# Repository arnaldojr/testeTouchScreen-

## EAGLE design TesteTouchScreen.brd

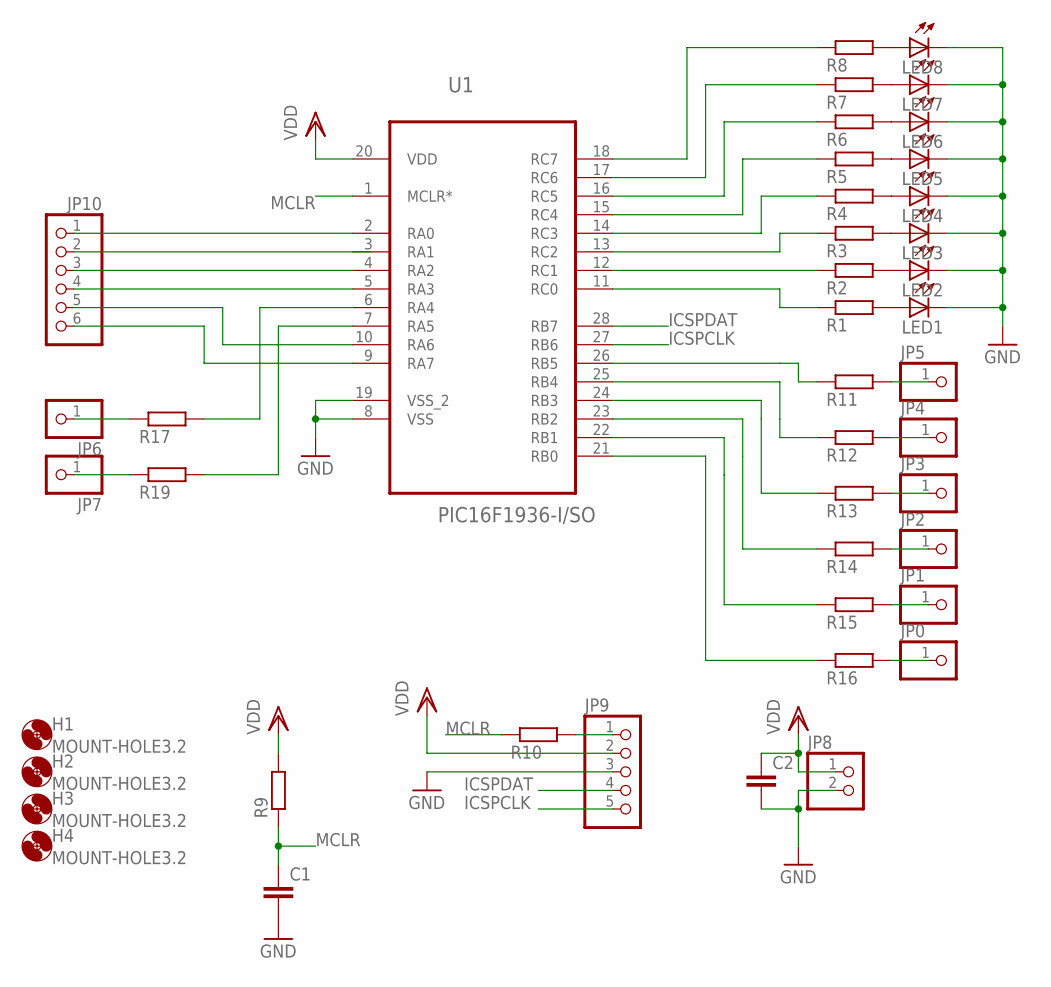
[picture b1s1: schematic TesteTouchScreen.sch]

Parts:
C1, C2: C-EUC1206; C1206
H1, H2, H3, H4: MOUNT-HOLE3.2; 3,2
JP0, JP1, JP2, JP3, JP4, JP5, JP6, JP7: PINHD-1X1; 1X01
JP8: PINHD-1X2; 1X02
JP9: PINHD-1X5; 1X05
JP10: PINHD-1X6; 1X06
LED1, LED2, LED3, LED4, LED5, LED6, LED7, LED8: LED5MM
R1, R2, R3, R4, R5, R6, R7, R8, R9, R10, R11, R12, R13, R14, R15, R16, R17, R19: R-EU_R0805; R0805
U1: PIC16F1936-I/SO; SOIC127P1030X265-28N

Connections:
GND: C1.2, C2.2, JP8.2, JP9.3, LED1.K (C), LED2.K (C), LED3.K (C), LED4.K (C), LED5.K (C), LED6.K (C), LED7.K (C), LED8.K (C), U1.8 (VSS), U1.19 (VSS_2)
ICSPCLK: JP9.5, U1.27 (RB6)
ICSPDAT: JP9.4, U1.28 (RB7)
MCLR: C1.1, R9.1, R10.1, U1.1 (MCLR*)
unnamed: JP6.1, R17.1
unnamed: JP7.1, R19.1
unnamed: JP0.1, R16.2
unnamed: JP1.1, R15.2
unnamed: JP2.1, R14.2
unnamed: JP3.1, R13.2
unnamed: JP5.1, R11.2
unnamed: R17.2, U1.6 (RA4)
unnamed: LED1.A, R1.2
unnamed: LED2.A, R2.2
unnamed: JP4.1, R12.2
unnamed: LED3.A, R3.2
unnamed: LED4.A, R4.2
unnamed: LED5.A, R5.2
unnamed: LED6.A, R6.2
unnamed: LED7.A, R7.2
unnamed: LED8.A, R8.2
unnamed: R1.1, U1.11 (RC0)
unnamed: R2.1, U1.12 (RC1)
unnamed: R3.1, U1.13 (RC2)
unnamed: R4.1, U1.14 (RC3)
unnamed: R5.1, U1.15 (RC4)
unnamed: R6.1, U1.16 (RC5)
unnamed: R7.1, U1.17 (RC6)
unnamed: R8.1, U1.18 (RC7)
unnamed: JP9.1, R10.2
unnamed: R19.2, U1.7 (RA5)
unnamed: R11.1, U1.26 (RB5)
unnamed: R12.1, U1.25 (RB4)
unnamed: R13.1, U1.24 (RB3)
unnamed: R14.1, U1.23 (RB2)
unnamed: R15.1, U1.22 (RB1)
unnamed: R16.1, U1.21 (RB0)
unnamed: JP10.1, U1.2 (RA0)
unnamed: JP10.3, U1.4 (RA2)
unnamed: JP10.4, U1.5 (RA3)
unnamed: JP10.5, U1.10 (RA6)
unnamed: JP10.6, U1.9 (RA7)
VDD: C2.1, JP8.1, JP9.2, R9.2, U1.20 (VDD)

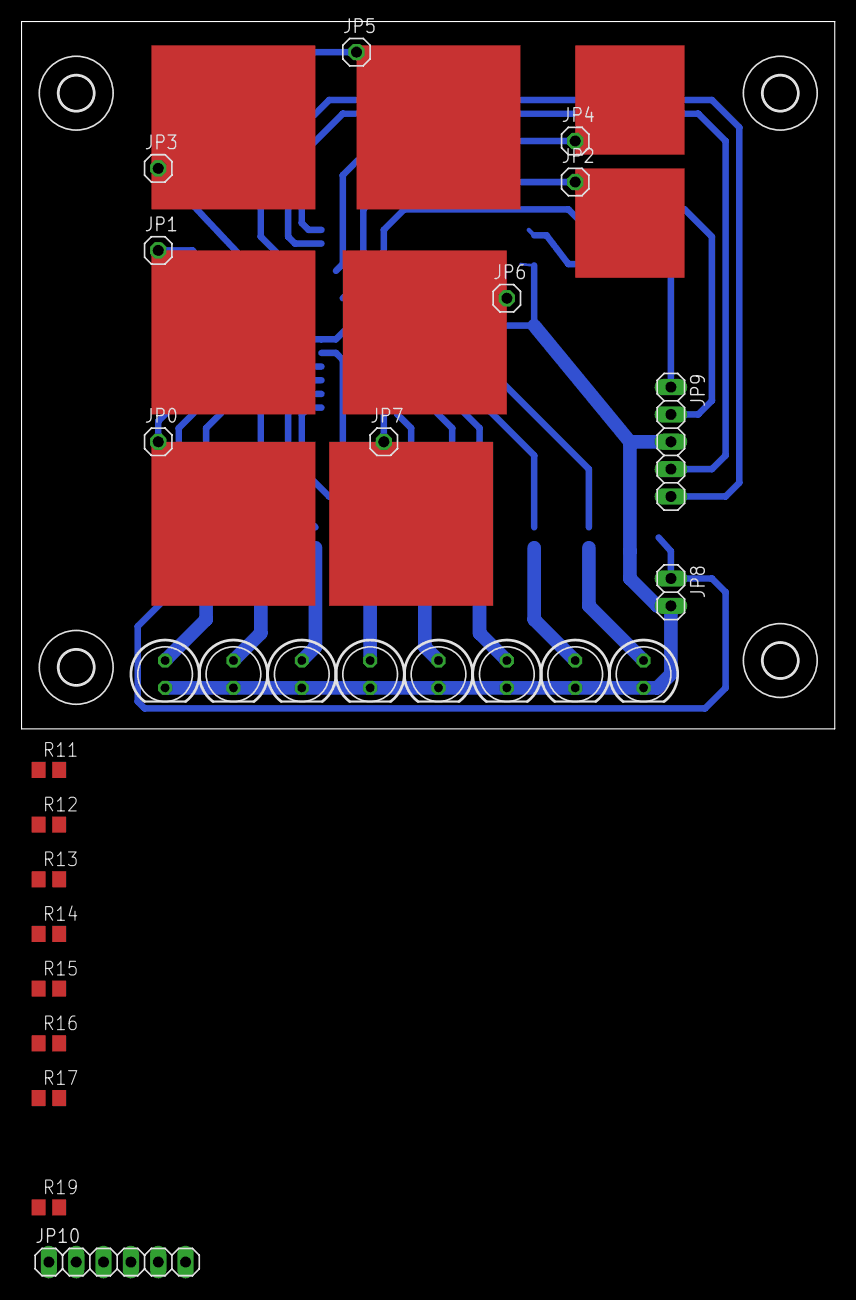
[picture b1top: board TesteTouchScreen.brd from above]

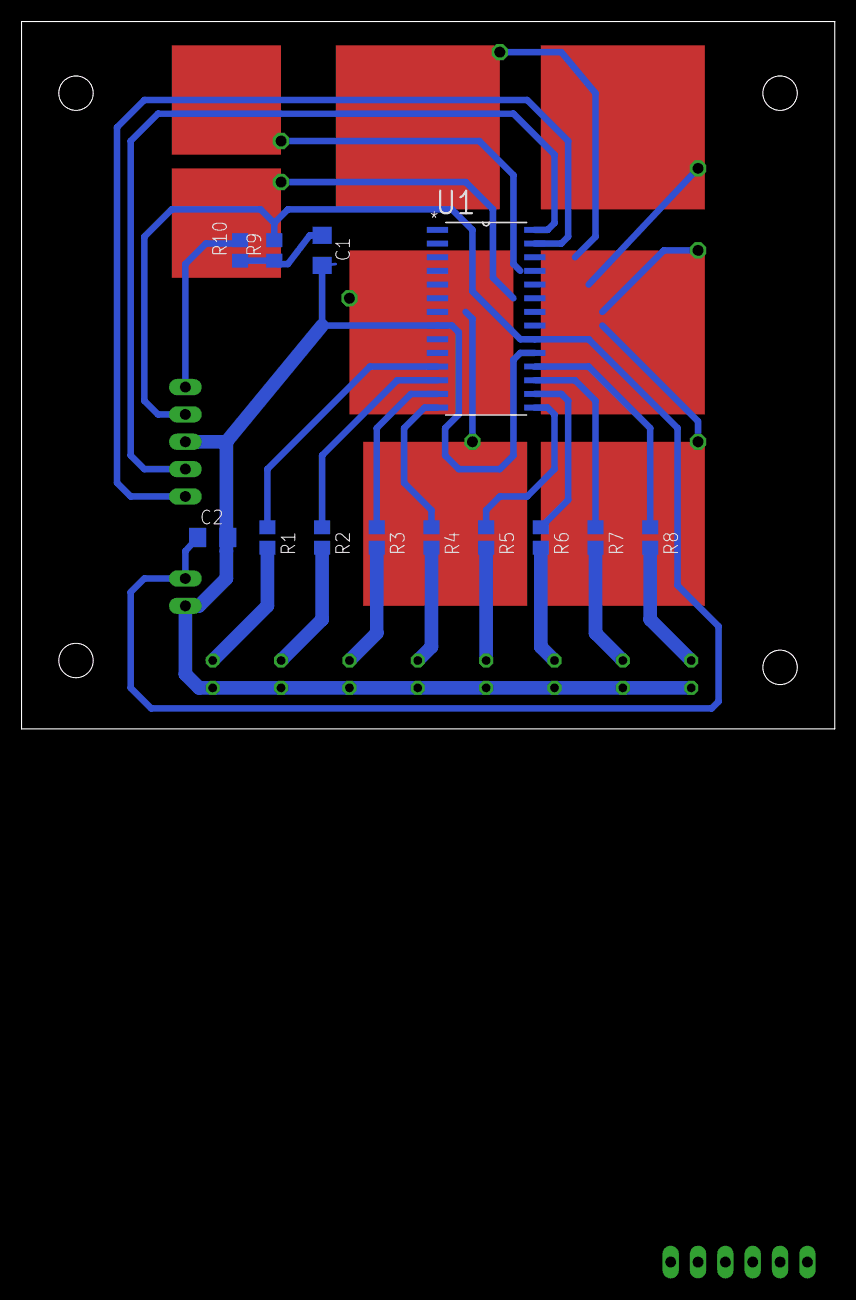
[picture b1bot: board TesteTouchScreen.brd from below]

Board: 2 copper layers, 75.5 x 65.7 mm, 44 parts (13 on the bottom side), 43 nets.

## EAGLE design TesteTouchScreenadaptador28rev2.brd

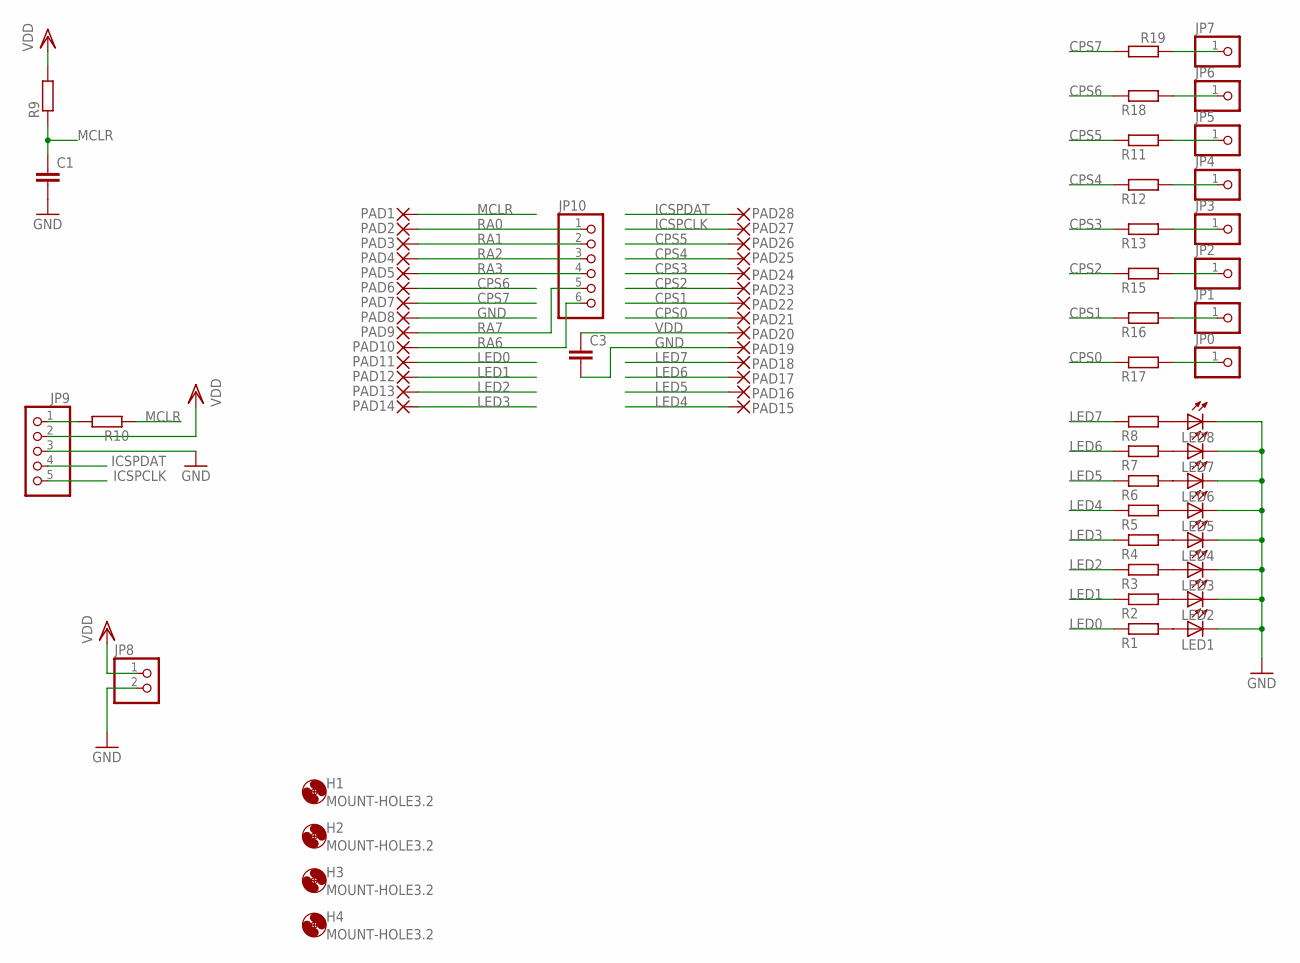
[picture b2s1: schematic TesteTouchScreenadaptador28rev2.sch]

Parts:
C1, C3: C-EUC1206; C1206
H1, H2, H3, H4: MOUNT-HOLE3.2; 3,2
JP0, JP1, JP2, JP3, JP4, JP5, JP6, JP7: PINHD-1X1; 1X01
JP8: PINHD-1X2; 1X02
JP9: PINHD-1X5; 1X05
JP10: PINHD-1X6; 1X06
LED1, LED2, LED3, LED4, LED5, LED6, LED7, LED8: LED5MM
PAD1, PAD2, PAD3, PAD4, PAD5, PAD6, PAD7, PAD8, PAD9, PAD10, PAD11, PAD12, PAD13, PAD14, PAD15, PAD16, PAD17, PAD18, PAD19, PAD20, PAD21, PAD22, PAD23, PAD24, PAD25, PAD26, PAD27, PAD28: SMD2; SMD1,27-2,54
R1, R2, R3, R4, R5, R6, R7, R8, R9, R10, R11, R12, R13, R15, R16, R17, R18, R19: R-EU_R0805; R0805

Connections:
CPS0: PAD21.1, R17.1
CPS1: PAD22.1, R16.1
CPS2: PAD23.1, R15.1
CPS3: PAD24.1, R13.1
CPS4: PAD25.1, R12.1
CPS5: PAD26.1, R11.1
CPS6: PAD6.1, R18.1
CPS7: PAD7.1, R19.2
GND: C1.2, C3.2, JP8.2, JP9.3, LED1.K (C), LED2.K (C), LED3.K (C), LED4.K (C), LED5.K (C), LED6.K (C), LED7.K (C), LED8.K (C), PAD8.1, PAD19.1
ICSPCLK: JP9.5, PAD27.1
ICSPDAT: JP9.4, PAD28.1
LED0: PAD11.1, R1.1
LED1: PAD12.1, R2.1
LED2: PAD13.1, R3.1
LED3: PAD14.1, R4.1
LED4: PAD15.1, R5.1
LED5: PAD16.1, R6.1
LED6: PAD17.1, R7.1
LED7: PAD18.1, R8.1
MCLR: C1.1, PAD1.1, R9.1, R10.1
unnamed: JP6.1, R18.2
unnamed: JP7.1, R19.1
unnamed: JP0.1, R17.2
unnamed: JP1.1, R16.2
unnamed: JP2.1, R15.2
unnamed: JP3.1, R13.2
unnamed: JP5.1, R11.2
unnamed: LED1.A, R1.2
unnamed: LED2.A, R2.2
unnamed: JP4.1, R12.2
unnamed: LED3.A, R3.2
unnamed: LED4.A, R4.2
unnamed: LED5.A, R5.2
unnamed: LED6.A, R6.2
unnamed: LED7.A, R7.2
unnamed: LED8.A, R8.2
unnamed: JP9.1, R10.2
RA0: JP10.1, PAD2.1
RA1: JP10.2, PAD3.1
RA2: JP10.3, PAD4.1
RA3: JP10.4, PAD5.1
RA6: JP10.6, PAD10.1
RA7: JP10.5, PAD9.1
VDD: C3.1, JP8.1, JP9.2, PAD20.1, R9.2

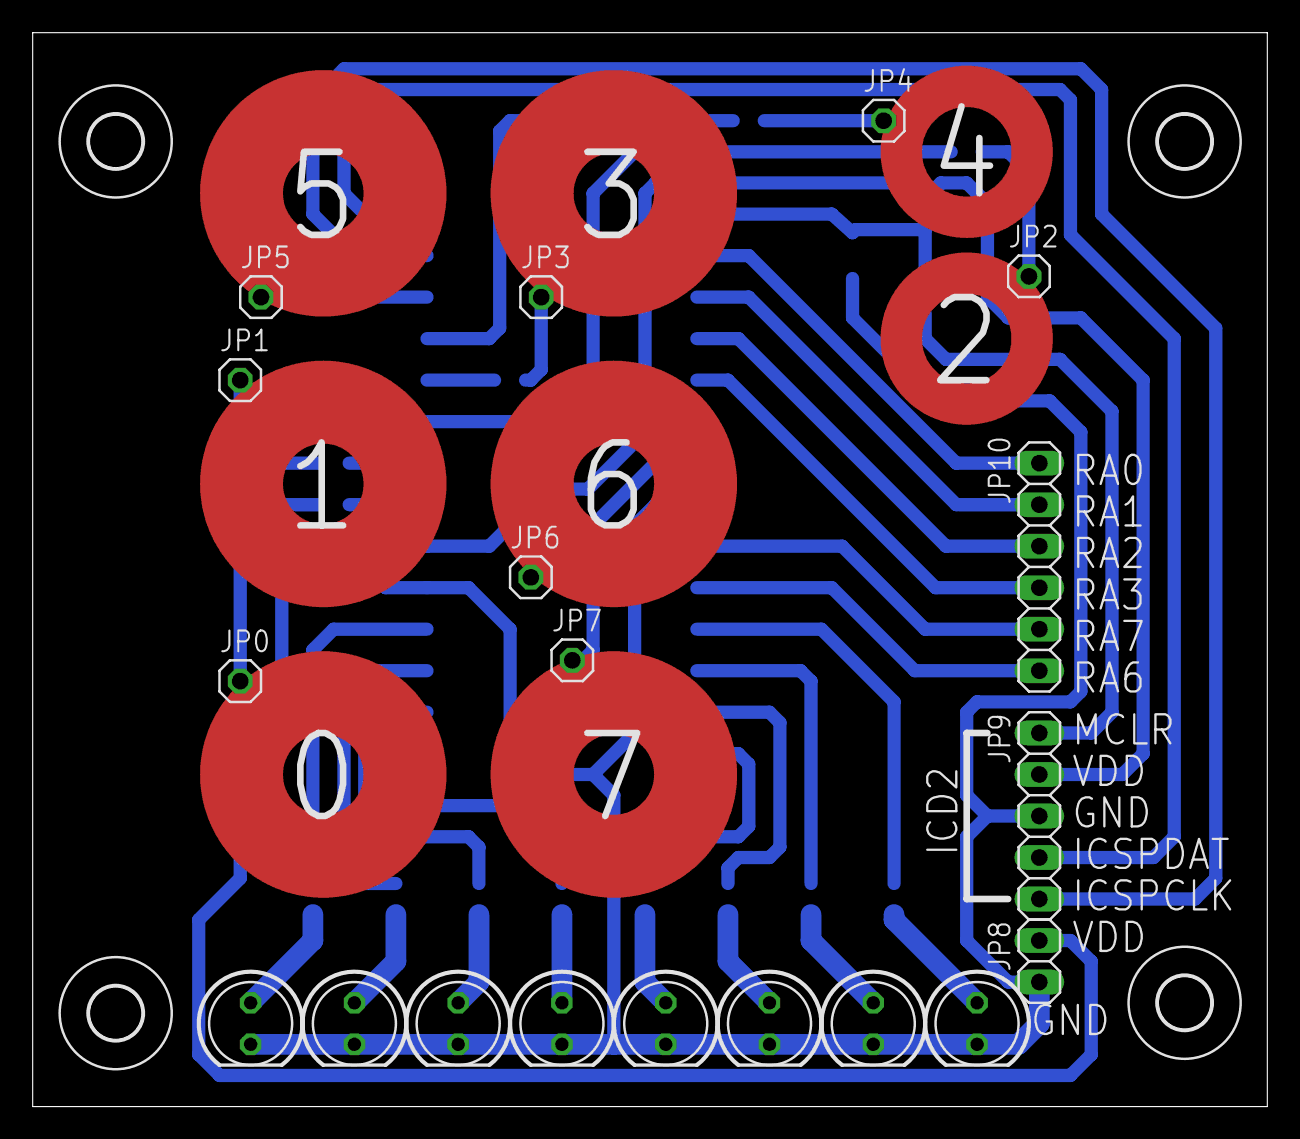
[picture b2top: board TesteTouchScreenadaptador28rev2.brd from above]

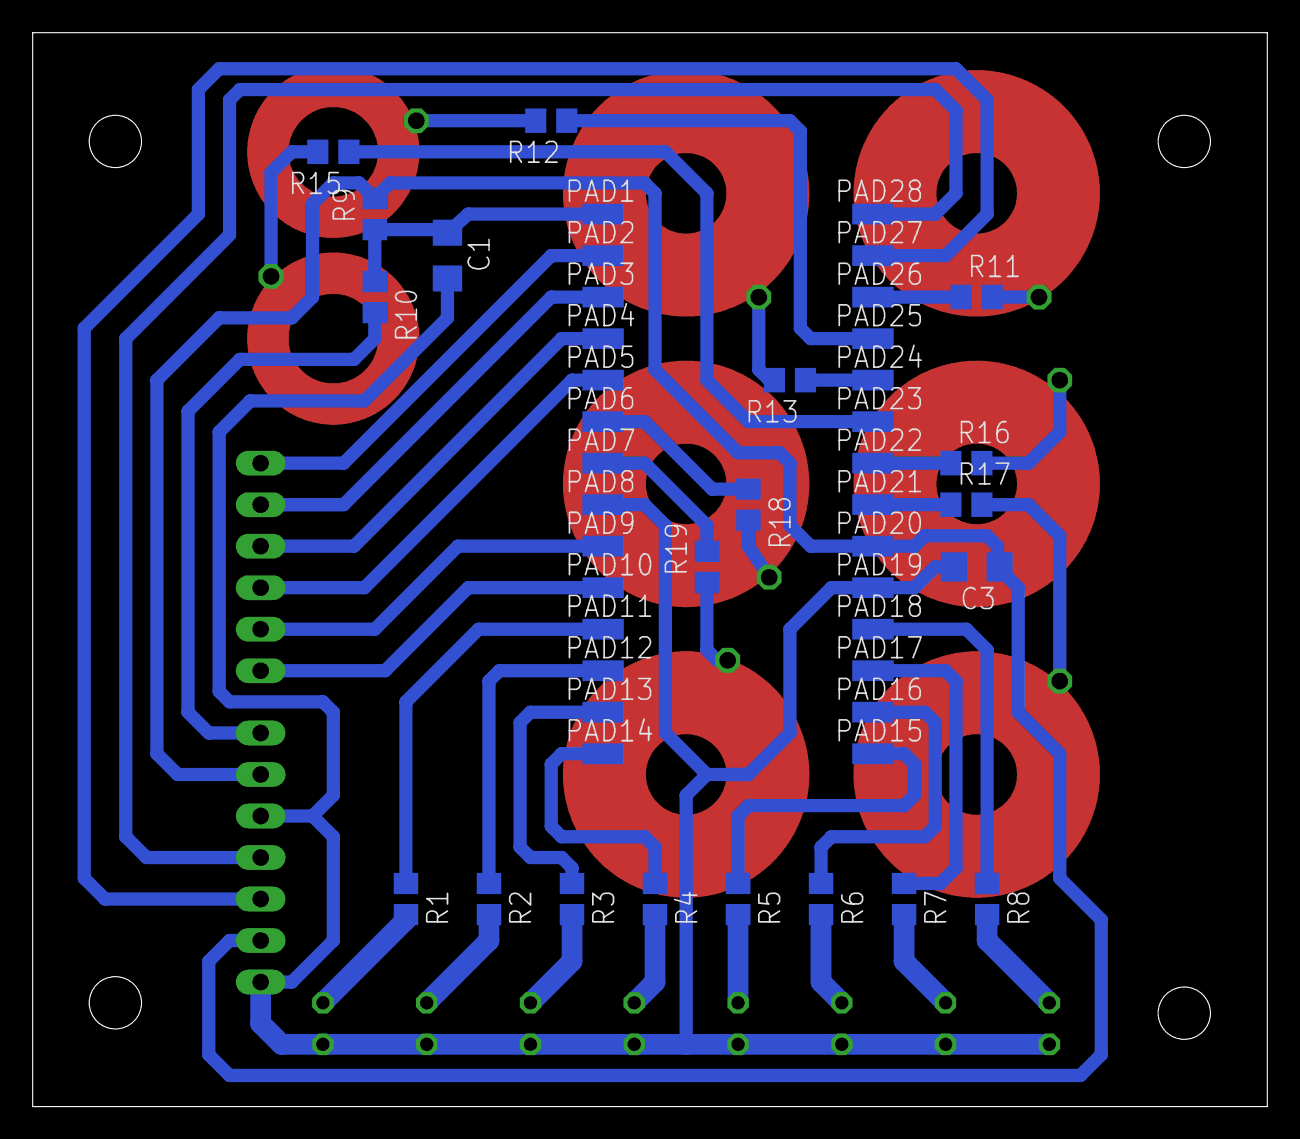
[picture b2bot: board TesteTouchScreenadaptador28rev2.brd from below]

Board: 2 copper layers, 75.5 x 65.7 mm, 71 parts (48 on the bottom side), 44 nets.

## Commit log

2018-11-02 init commit
